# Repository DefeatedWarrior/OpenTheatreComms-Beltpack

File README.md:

# OpenTheatreComms beltpack

An open, DIY full-duplex wireless theatre intercom beltpack in the spirit of the Hollyland Solidcom M1 and Clear-Com FreeSpeak II.
It uses an ESP32-S3 with an LR2021 radio on 915–928 MHz (Australia), talks to PoE base stations over a 20 ms TDMA frame,
and is 3D printed and hand-assembled.

## What's here

| Path | Contents |
|---|---|
| `cad/final_bp.py` | CadQuery model of the whole beltpack: shells, TPU caps, dials, keys, both PCBs and every bought part as a datasheet envelope |
| `cad/geom.py` | Shared shape helpers (the curved pill plan, edge fillets, the flat-top frame) |
| `cad/clash.py` | Pairwise interference check across all 71 parts |
| `cad/export_boards.py` | KiCad hand-off: DXF outlines with true arcs, placement layers and dimensioned drawings |
| `cad/make_kicad.py`, `cad/make_enclosure_ref.py` | Build the KiCad projects (needs KiCad's `pcbnew` Python module) and the enclosure STEP |
| `cad/section.py`, `cad/size_table.py` | Section drawings and the placement CSV |
| `cad/out/beltpack_final.step` | Full assembly (STEP) |
| `cad/out/stl/` | Every printed part as STL |
| `cad/out/kicad/` | Board outlines (DXF), drawings, placement CSV |
| `kicad/` | Finished KiCad projects, each with a README and `fab/` outputs (Gerbers, drill, BOM, placement, schematic PDF, previews): beltpack main board, top board, pack lid and dock contact board, and the base station carrier |
| `pcb/` | The Python that generates each board: `design.py` (parts and nets), schematic, placement, routing, finishing and fab outputs |
| `order/` | The v1 order for 2 beltpacks + 1 base station: JLCPCB board settings and stencils, the LCSC cart (all parts hand-fitted), other suppliers, and the assembly guide (`ORDER_README.md`) |
| `renders/` | Render sheet and individual renders |
| `viewer/` | Interactive three.js viewer (open `viewer/index.html` from a local web server) |

The firmware and system architecture, the BOM and the open decisions live in the
[architecture doc](https://claude.ai/artifact/WxYNr5Pqa9sfHdBBrxbrdB). The [3D viewer](https://claude.ai/artifact/3vzgMREVLjprdXMhVy1U9x)
is the same page as `viewer/`.

## The pack

- **Size:** 105 × 77 × 30 mm shell (108 × 81 × 35 mm with the TPU caps, 39 mm deep with the belt plate). The back follows a 400 mm radius to sit on the hip.
- **Controls:** four talk keys and a 1.3 in OLED on the flat top, a detented dial at each round end, Back / Function / Menu in a recessed panel on the front.
- **Bottom:** XLR-4 male (D-type), power button, USB-C, 3.5 mm TRRS, flashlight.
- **Power:** a 104050 Li-ion pack (2500 mAh) forms the back of the case; the belt plate slides up its rails and locks it in. Three spring pins carry battery +, NTC and battery −; a JST XH 2-pin socket (J11) on the main board is a second battery input for a wired cell or bench supply.
- **Dock contacts:** four contact pads in the case bottom (VBUS, D+, D−, GND) on a small contact board lying in the case bottom under
  the battery pack, cabled flat to J12, a vertical socket at the main board's bottom edge. A dock charges the pack and talks USB to it (pairing, settings, firmware); a diode keeps the USB-C's 5 V off the pads.
- **Boards:** a curved top PCB (99.8 × 26.5 mm) under the keys carrying the OLED, six RGB lights on an LP5024 driver and both encoders, and a vertical main PCB (87.5 × 64.5 mm) carrying the MCU, radio, codec, power and connectors. A 10-way JST SH cable links them.
- **Radio:** an Elecrow LR2021 module on 915–928 MHz with switched antenna diversity: a PE4259-type switch (HX4259-63) picks between two flex antennas, one inside each round end, every frame.

## Rebuilding

Needs Python 3 with `cadquery`, `ezdxf`, `matplotlib` and `Pillow`.

```sh
cd cad
python3 final_bp.py       # model, STEP, GLB, STLs, parts_final.json (about a minute)
python3 clash.py          # interference check: expect "CLASHES: 0"
python3 export_boards.py  # DXFs and drawings into out/kicad
python3 section.py        # section drawings
python3 size_table.py     # placement.csv
python3 build_viewer.py   # viewer/index.html + viewer/beltpack.json
python3 make_enclosure_ref.py && python3 make_kicad.py   # KiCad projects in ../kicad (needs KiCad 7+)
```

## Base station

A 150 x 90 mm 2-layer carrier for a Waveshare ESP32-P4-NANO (Ethernet for AES67, optional PoE), with the same LR2021 radio and
two edge SMA antennas, a DC input (7-24 V buck), a 1.3 in OLED, four talk keys with RGB lights, eight beltpack lights and a menu dial.
It has no audio of its own: the operator's headset is a beltpack plugged into the base by USB-C. See `kicad/base_pcb/README.md`.

## Status

**Boards:** all five are laid out and pass KiCad DRC with 0 errors and 0 unconnected pads. The v1 order (`order/`) is ready, at about
A$410 for 2 beltpacks + 1 base station, with every part hand-fitted from solder-paste stencils.

**Case:** to be redone around the cheaper parts chosen for v1. The pack pads move to 4.0 mm from the main board's back face for the
Xinyangze spring pins; it needs room for the 7 mm JST XH socket on the main board's front and the Alps EC11 dials' shaft length, and a pocket in
the bottom for the dock contact board. The base station's dock side (spring pins, switched VBUS, USB host) is still to design.

**Reference model notes:**

The CAD model was the reference for the KiCad layout. A few part envelopes are typical sizes still to check against
the exact parts you buy: the encoder body height, the XLR D-flange and depth, USB4105, the PTS815 height variant, the side tact switch,
the JST SH bodies and where the OLED panel's active area sits on its glass. See `cad/out/kicad/README.md`.

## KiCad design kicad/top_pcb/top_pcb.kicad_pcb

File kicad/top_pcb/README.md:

# Top PCB build scripts

The top PCB (keys, six RGB lights, OLED connector, both dials, IO expander, LED driver, link to the main PCB) is generated
from one file, `design.py`, which holds every part, its nets, its schematic position and its board position.

```sh
python3 make_lib.py                                   # the OLED tail pads footprint and the LP5024 symbol
python3 make_sch.py                                   # out/top_pcb.kicad_sch (KiCad 7 format, real library symbols)
kicad-cli sch export netlist --format kicadsexpr -o out/top_pcb.net out/top_pcb.kicad_sch
python3 chknet.py out/top_pcb.net                     # every net must match design.py
python3 make_pcb.py                                   # place, pre-route the FPC fan-outs, GND fanouts, route with Freerouting 1.9 -> out/routed.kicad_pcb
                                                      # (make_pcb.py import: re-import the last routing session without rerouting)
python3 finish_pcb.py                                 # GND pours, stitching, repair, DRC -> ../kicad_proj/top_pcb/
python3 make_fab.py                                   # Gerbers, drill, placement, BOM, assembly PDFs -> ../kicad_proj/top_pcb/fab/
```

Needs KiCad 7+ (`pcbnew` Python module and `kicad-cli`), the KiCad symbol and footprint libraries, Java, `xvfb-run`,
Freerouting 1.9.0 (`FREEROUTING` in `make_pcb.py`), and Python `shapely` and `cairosvg`.

| File | Role |
|---|---|
| `design.py` | Parts, nets, schematic and board positions; `OLED_PIN1_AT_PLUS_X` flips the panel pin order |
| `make_lib.py` | Writes `lib/OpenTheatreComms.pretty` (the 30 solder pads, 0.7 mm, for the OLED panel's tail) and `lib/OpenTheatreComms.kicad_sym` (TI LP5024) |
| `symlib.py`, `sexp.py` | Read KiCad library symbols, read and write S-expressions |
| `make_sch.py`, `chknet.py` | Schematic writer and netlist check |
| `pcbgeom.py` | Board-frame transforms, copper model for via placement, per-net connectivity check |
| `make_pcb.py`, `finish_pcb.py` | Board build |
| `make_fab.py`, `render.py` | Fab outputs and PNG previews |
| `template/` | The starter board (outline, holes, guides, enclosure 3D reference) the build starts from |

Board frame: origin at the board centre, +X right, +Y toward the hip (back) edge, viewed from above (F = top).

## Lights

Six common-anode RGB LEDs (Lite-On LTST-C19HE1WT, 1.6 x 1.6 mm): D1-D4 above the four talk keys, D5 and D6 under the
left and right status light pipes. Each is driven by a TI LP5024 (U2, on the bottom side) on the board's I2C bus, so
every LED takes any colour and brightness from firmware:

| Light | LP5024 channel | Outputs (R, G, B) |
|---|---|---|
| D1, talk key 1 | LED0 | OUT0-OUT2 |
| D2, talk key 2 | LED1 | OUT3-OUT5 |
| D5, status left | LED2 | OUT6-OUT8 |
| D3, talk key 3 | LED3 | OUT9-OUT11 |
| D4, talk key 4 | LED4 | OUT12-OUT14 |
| D6, status right | LED5 | OUT15-OUT17 |

The order follows the board (each light's lines leave the driver on the side facing it); `LED_CH` in `design.py` holds it.

- **Current:** R1 = 15k sets 4.9 mA full scale per colour (105 x 0.7 V / R1); the 12-bit PWM dims from there. The low
  current leaves the green and blue chips (about 2.7 V at 5 mA) headroom on the 3.3 V anode supply.
- **I2C addresses on the beltpack bus:** LP5024 0x28 (ADDR1 = ADDR0 = GND). Its broadcast address is 0x3C, so the OLED
  is strapped to **0x3D** (D/C# high). The IO expander is 0x20.
- **EN** comes from the expander's P05: its internal pull-up holds the driver on from power-up; firmware can pulse it low
  to reset the driver. Expander P10-P17 are now free.

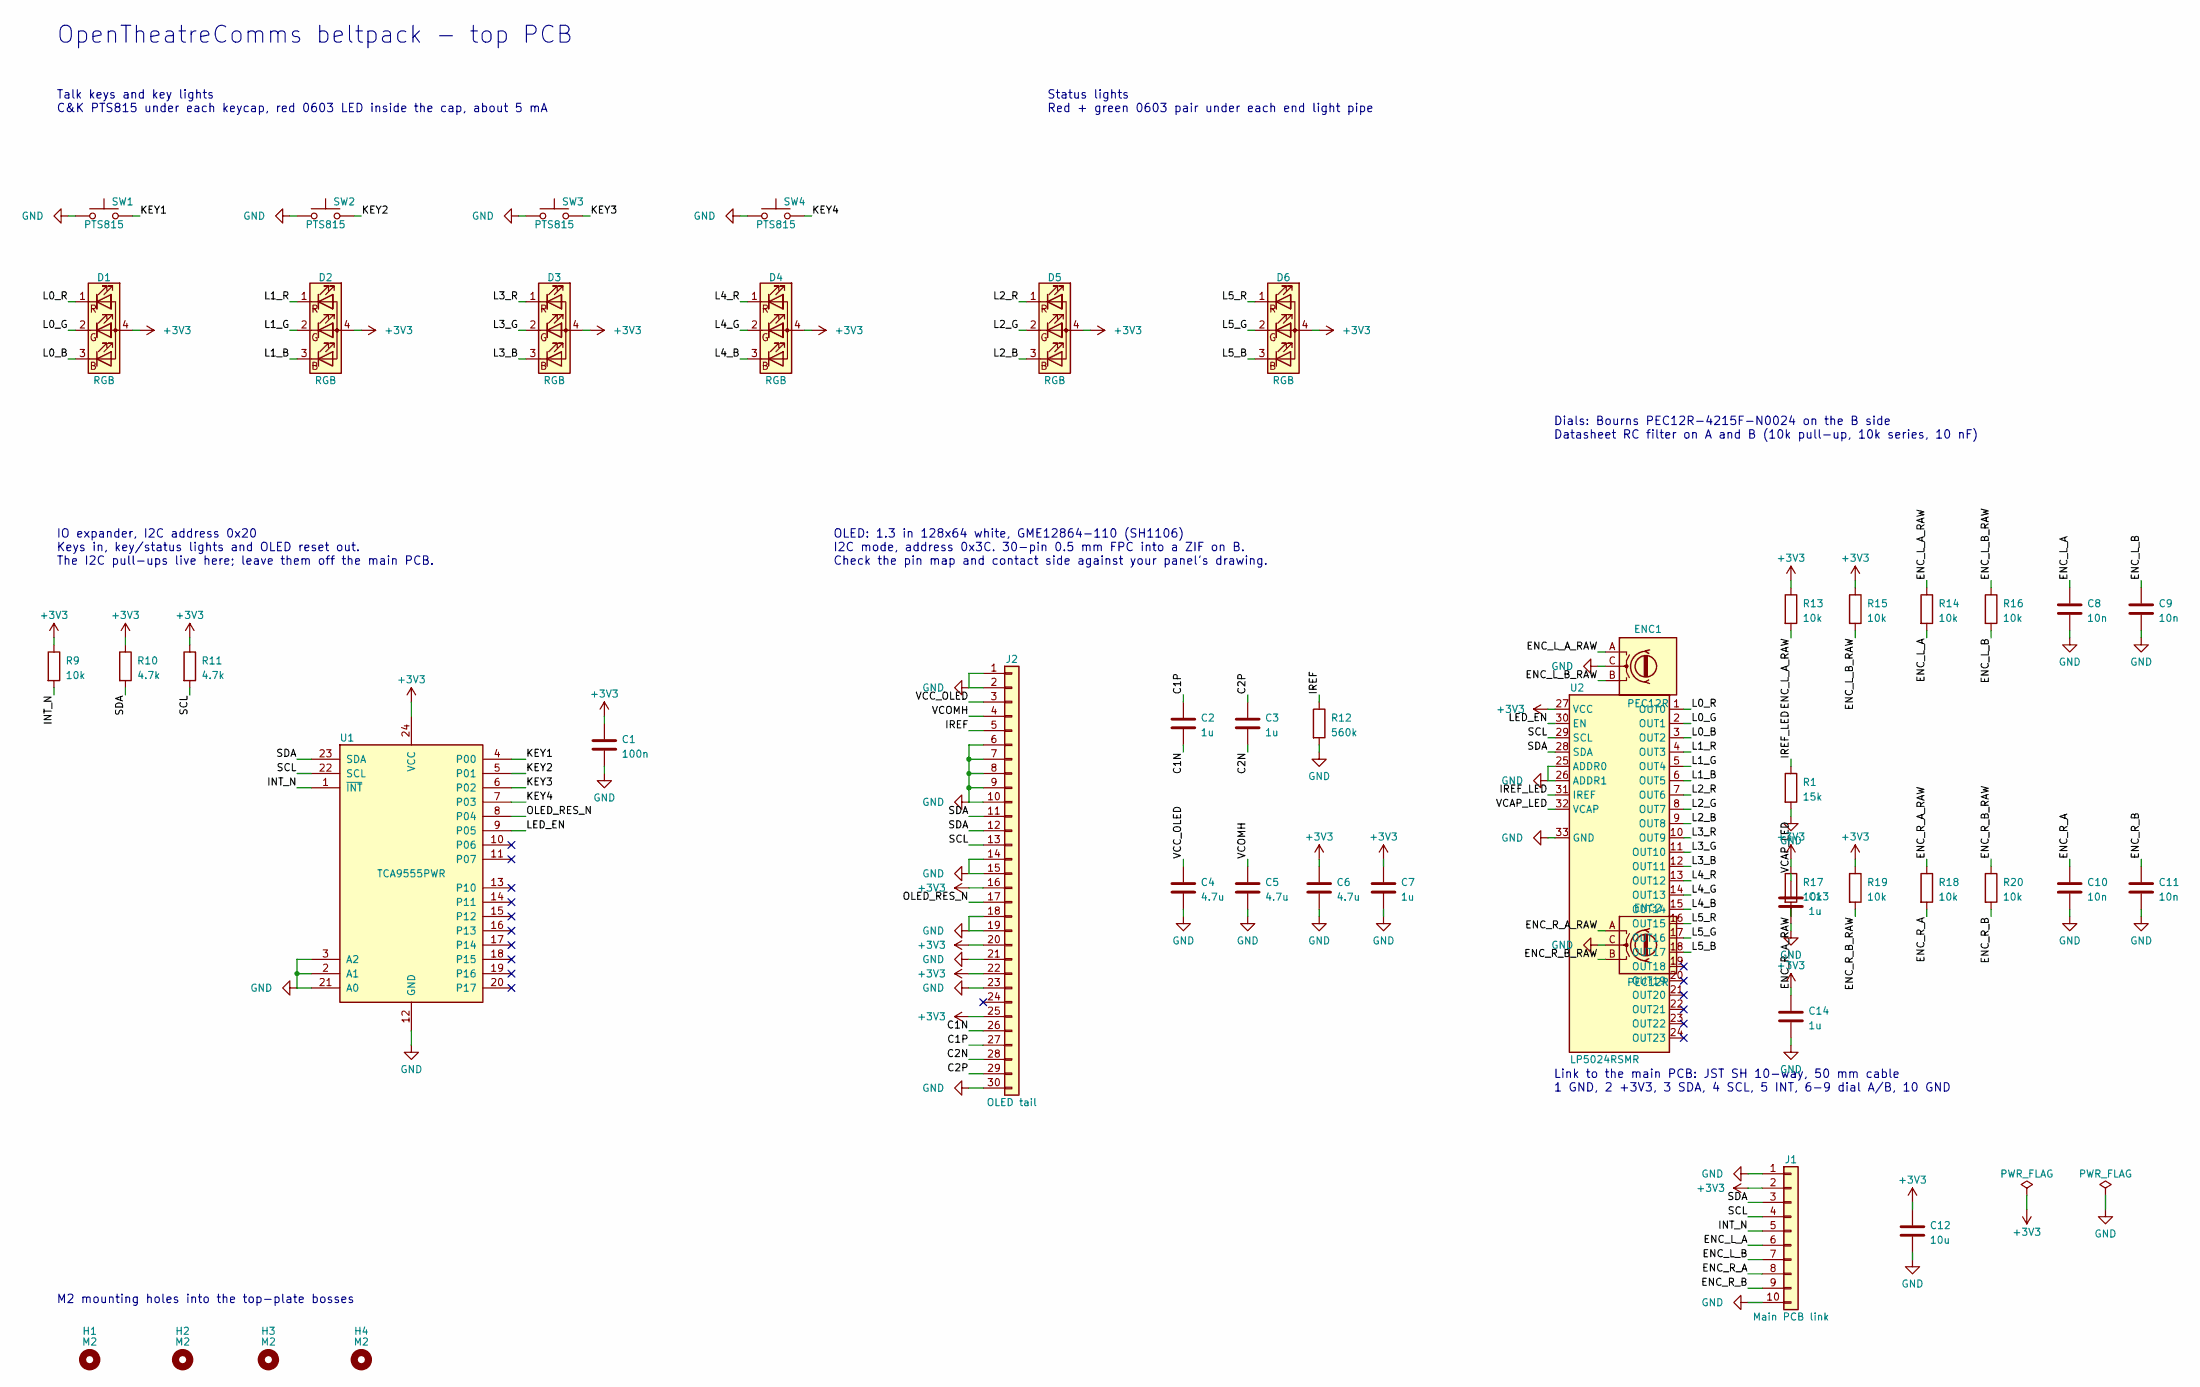
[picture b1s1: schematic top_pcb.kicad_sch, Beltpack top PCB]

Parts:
C1: 100n; C_0603_1608Metric_Pad1.08x0.95mm_HandSolder; MPN 0603 X7R 50 V
C2, C3, C13, C14: 1u; C_0603_1608Metric_Pad1.08x0.95mm_HandSolder; MPN 0603 X5R
C4, C5: 4.7u; C_0603_1608Metric_Pad1.08x0.95mm_HandSolder; MPN 0603 X5R 25 V
C6: 4.7u; C_0603_1608Metric_Pad1.08x0.95mm_HandSolder; MPN 0603 X5R 10 V
C7: 1u; C_0603_1608Metric_Pad1.08x0.95mm_HandSolder; MPN 0603 X5R 10 V
C8, C9, C10, C11: 10n; C_0603_1608Metric_Pad1.08x0.95mm_HandSolder; MPN 0603 X7R 50 V
C12: 10u; C_0603_1608Metric_Pad1.08x0.95mm_HandSolder; MPN 0603 X5R 10 V
D1, D2, D3, D4, D5, D6: RGB; LED_LiteOn_LTST-C19HE1WT; MPN Lite-On LTST-C19HE1WT
ENC1, ENC2: PEC12R; RotaryEncoder_Bourns_Vertical_PEC12R-3x17F-Nxxxx; MPN Alps EC11N1520402
H1, H2, H3, H4: M2; MountingHole_2.2mm_M2
J1: Main PCB link; JST_SH_BM10B-SRSS-TB_1x10-1MP_P1.00mm_Vertical; MPN JST BM10B-SRSS-TB
J2: OLED tail; OLED_Tail_30P_0.7mm_Solder; MPN OLED panel tail soldered to pads (no pa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
R1: 15k; R_0603_1608Metric_Pad0.98x0.95mm_HandSolder; MPN 0603 1%
R9, R13, R14, R15, R16, R17, R18, R19, R20: 10k; R_0603_1608Metric_Pad0.98x0.95mm_HandSolder; MPN 0603 1%
R10, R11: 4.7k; R_0603_1608Metric_Pad0.98x0.95mm_HandSolder; MPN 0603 1%
R12: 560k; R_0603_1608Metric_Pad0.98x0.95mm_HandSolder; MPN 0603 1%
SW1, SW2, SW3, SW4: PTS815; SW_SPST_PTS810; MPN C&K PTS815 SJM 250 SMTR LFS
U1: TCA9555PWR; TSSOP-24_4.4x7.8mm_P0.65mm; MPN TI TCA9555PWR
U2: LP5024RSMR; VQFN-32-1EP_4x4mm_P0.4mm_EP2.8x2.8mm; MPN TI LP5024RSMR

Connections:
+3V3: C1.1, C6.1, C7.1, C12.1, C14.1, D1.4 (A), D2.4 (A), D3.4 (A), D4.4 (A), D5.4 (A), D6.4 (A), J1.2, J2.16, J2.20, J2.22, J2.25, R9.1, R10.1, R11.1, R13.1, R15.1, R17.1, R19.1, U1.24 (VCC), U2.27 (VCC)
/C1N: C2.2, J2.26
/C1P: C2.1, J2.27
/C2N: C3.2, J2.28
/C2P: C3.1, J2.29
/ENC_L_A: C8.1, J1.6, R14.2
/ENC_L_A_RAW: ENC1.A, R13.2, R14.1
/ENC_L_B: C9.1, J1.7, R16.2
/ENC_L_B_RAW: ENC1.B, R15.2, R16.1
/ENC_R_A: C10.1, J1.8, R18.2
/ENC_R_A_RAW: ENC2.A, R17.2, R18.1
/ENC_R_B: C11.1, J1.9, R20.2
/ENC_R_B_RAW: ENC2.B, R19.2, R20.1
/INT_N: J1.5, R9.2, U1.1 (~INT)
/IREF: J2.5, R12.1
/IREF_LED: R1.1, U2.31 (IREF)
/KEY1: SW1.2, U1.4 (P00)
/KEY2: SW2.2, U1.5 (P01)
/KEY3: SW3.2, U1.6 (P02)
/KEY4: SW4.2, U1.7 (P03)
/L0_B: D1.3 (BK), U2.3 (OUT2)
/L0_G: D1.2 (GK), U2.2 (OUT1)
/L0_R: D1.1 (RK), U2.1 (OUT0)
/L1_B: D2.3 (BK), U2.6 (OUT5)
/L1_G: D2.2 (GK), U2.5 (OUT4)
/L1_R: D2.1 (RK), U2.4 (OUT3)
/L2_B: D5.3 (BK), U2.9 (OUT8)
/L2_G: D5.2 (GK), U2.8 (OUT7)
/L2_R: D5.1 (RK), U2.7 (OUT6)
/L3_B: D3.3 (BK), U2.12 (OUT11)
/L3_G: D3.2 (GK), U2.11 (OUT10)
/L3_R: D3.1 (RK), U2.10 (OUT9)
/L4_B: D4.3 (BK), U2.15 (OUT14)
/L4_G: D4.2 (GK), U2.14 (OUT13)
/L4_R: D4.1 (RK), U2.13 (OUT12)
/L5_B: D6.3 (BK), U2.18 (OUT17)
/L5_G: D6.2 (GK), U2.17 (OUT16)
/L5_R: D6.1 (RK), U2.16 (OUT15)
/LED_EN: U1.9 (P05), U2.30 (EN)
/OLED_RES_N: J2.17, U1.8 (P04)
/SCL: J1.4, J2.13, R11.2, U1.22 (SCL), U2.29 (SCL)
/SDA: J1.3, J2.11, J2.12, R10.2, U1.23 (SDA), U2.28 (SDA)
/VCAP_LED: C13.1, U2.32 (VCAP)
/VCC_OLED: C4.1, J2.3
/VCOMH: C5.1, J2.4
GND: C1.2, C4.2, C5.2, C6.2, C7.2, C8.2, C9.2, C10.2, C11.2, C12.2, C13.2, C14.2, ENC1.C, ENC2.C, J1.1, J1.10, J2.1, J2.2, J2.6, J2.7, J2.8, J2.9, J2.10, J2.14, J2.15, J2.18, J2.19, J2.21, J2.23, J2.30, R1.2, R12.2, SW1.1, SW2.1, SW3.1, SW4.1, U1.2 (A1), U1.3 (A2), U1.12 (GND), U1.21 (A0), U2.25 (ADDR0), U2.26 (ADDR1), U2.33 (GND)

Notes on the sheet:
Talk keys and key lights C&K PTS815 under each keycap, red 0603 LED inside the cap, about 5 mA
Status lights Red + green 0603 pair under each end light pipe
IO expander, I2C address 0x20 Keys in, key/status lights and OLED reset out. The I2C pull-ups live here; leave them off the main PCB.
OLED: 1.3 in 128x64 white, GME12864-110 (SH1106) I2C mode, address 0x3C. 30-pin 0.5 mm FPC into a ZIF on B. Check the pin map and contact side against your panel's drawing.
Dials: Bourns PEC12R-4215F-N0024 on the B side Datasheet RC filter on A and B (10k pull-up, 10k series, 10 nF)
Link to the main PCB: JST SH 10-way, 50 mm cable 1 GND, 2 +3V3, 3 SDA, 4 SCL, 5 INT, 6-9 dial A/B, 10 GND
M2 mounting holes into the top-plate bosses
OpenTheatreComms beltpack - top PCB

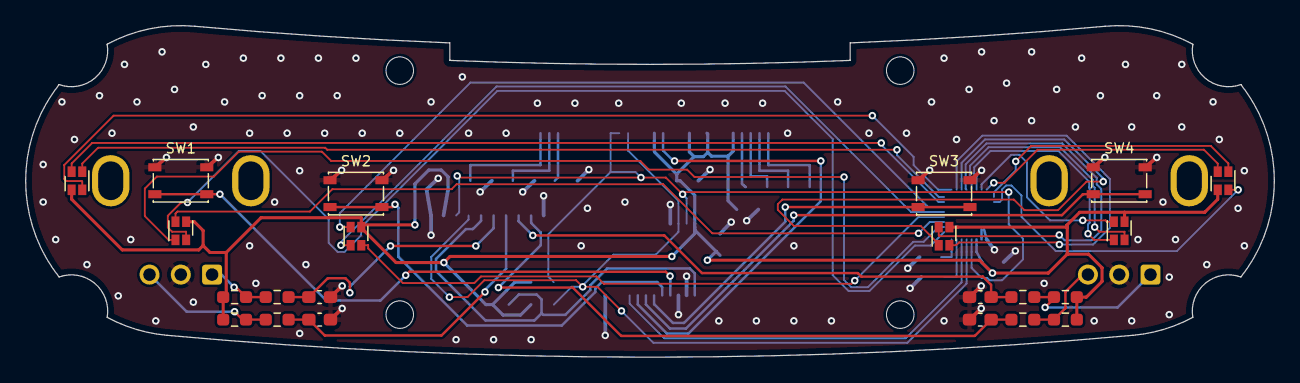
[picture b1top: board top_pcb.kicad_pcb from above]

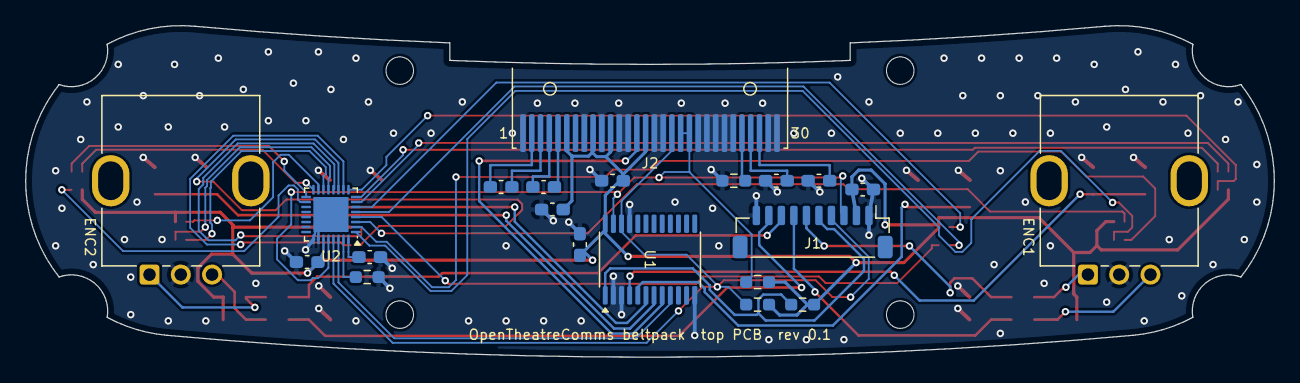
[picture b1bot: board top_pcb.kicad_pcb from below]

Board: 2 copper layers, 99.8 x 26.5 mm, 47 parts (21 on the bottom side), 46 nets.

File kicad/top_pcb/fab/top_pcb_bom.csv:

Qty,References,Value,Footprint,Part,Side,Notes
1,C1,100n,C_0603_1608Metric_Pad1.08x0.95mm_HandSolder,0603 X7R 50 V,bottom,U1 decoupling
4,C2 C3 C13 C14,1u,C_0603_1608Metric_Pad1.08x0.95mm_HandSolder,0603 X5R,bottom,
2,C4 C5,4.7u,C_0603_1608Metric_Pad1.08x0.95mm_HandSolder,0603 X5R 25 V,bottom,
1,C6,4.7u,C_0603_1608Metric_Pad1.08x0.95mm_HandSolder,0603 X5R 10 V,bottom,Charge-pump supply (VBAT pin)
1,C7,1u,C_0603_1608Metric_Pad1.08x0.95mm_HandSolder,0603 X5R 10 V,bottom,Logic supply (VDD pin)
4,C8 C9 C10 C11,10n,C_0603_1608Metric_Pad1.08x0.95mm_HandSolder,0603 X7R 50 V,top,
1,C12,10u,C_0603_1608Metric_Pad1.08x0.95mm_HandSolder,0603 X5R 10 V,bottom,"Bulk at the link connector, wired straight to its pins 1 and 2"
6,D1 D2 D3 D4 D5 D6,RGB,LED_LiteOn_LTST-C19HE1WT,Lite-On LTST-C19HE1WT,top,
2,ENC1 ENC2,PEC12R,RotaryEncoder_Bourns_Vertical_PEC12R-3x17F-Nxxxx,Alps EC11N1520402,bottom,
1,J1,Main PCB link,JST_SH_BM10B-SRSS-TB_1x10-1MP_P1.00mm_Vertical,JST BM10B-SRSS-TB,bottom,JST SH 10-way top entry; 50 mm cable to SM10B on the main PCB tab
1,J2,OLED tail,OLED_Tail_30P_0.7mm_Solder,OLED panel tail soldered to pads (no part),bottom,"Solder pads for the panel's 30-lead tail (0.7 mm pitch). Standard 1.3 in SH1106 30-pin pin map; I2C (BS2..0 = 010), address 0x3D (SA0 = D/C# high: 0x3C is the LP5024 broadcast)"
1,R1,15k,R_0603_1608Metric_Pad0.98x0.95mm_HandSolder,0603 1%,bottom,"LP5024 full-scale current, 4.9 mA"
9,R9 R13 R14 R15 R16 R17 R18 R19 R20,10k,R_0603_1608Metric_Pad0.98x0.95mm_HandSolder,0603 1%,bottom/top,
2,R10 R11,4.7k,R_0603_1608Metric_Pad0.98x0.95mm_HandSolder,0603 1%,bottom,
1,R12,560k,R_0603_1608Metric_Pad0.98x0.95mm_HandSolder,0603 1%,bottom,Segment current reference: 560k per the panel reference circuit (12.5 uA max)
4,SW1 SW2 SW3 SW4,PTS815,SW_SPST_PTS810,C&K PTS815 SJM 250 SMTR LFS,top,
1,U1,TCA9555PWR,TSSOP-24_4.4x7.8mm_P0.65mm,TI TCA9555PWR,bottom,"16-bit I2C IO expander, 0x20, internal 100k pull-ups"
1,U2,LP5024RSMR,VQFN-32-1EP_4x4mm_P0.4mm_EP2.8x2.8mm,TI LP5024RSMR,bottom,"24-channel I2C RGB LED driver, 0x28: six RGB LEDs; EN from the expander (P05, high by its pull-up at power-up)"

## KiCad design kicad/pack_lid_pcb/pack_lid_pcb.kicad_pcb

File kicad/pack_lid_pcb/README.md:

# Beltpack pack lid PCB, rev 0.1

The battery pack's contact board. It sits in the recess in the pack's front face, under the main PCB's three Mill-Max
spring pins, and carries the cell's three leads to them: BAT+, the pack NTC, and BAT-.

| Front (faces the main PCB) | Back (faces the cell) |
|---|---|
|  |  |

| | |
|---|---|
| Size | 24 x 8 mm, 0.8 mm FR4, 2 layers |
| Finish | HASL (with lead) as ordered; the three 3 mm contact pads are bare. ENIG is the upgrade if contact ever gets flaky |
| Parts | None. Three contact pads, three plated wire holes for 0.25 mm2 (24 AWG) wire, and short front-side tracks |
| DRC | 0 errors, 0 unconnected. 4 warnings, both expected: the contact and wire pads have their library silk and courtyards moved off (they are copper, not parts), and the enclosure reference footprint has no library |

## Files

| Path | Contents |
|---|---|
| `pack_lid_pcb.kicad_sch`, `pack_lid_pcb.kicad_pcb` | Schematic and board |
| `fab/pack_lid_pcb_gerbers.zip` | Gerbers + Excellon drill, ready to upload |
| `fab/pack_lid_pcb_schematic.pdf`, `fab/pack_lid_pcb_drc.rpt` | Schematic print and the DRC report |

Order as: 2 layers, 0.8 mm, HASL (with lead) or ENIG, any mask colour. There's nothing to assemble: solder the cell's leads into the holes.

## Pads and wiring

| Contact pad (front) | Spring pin on the main PCB | Wire hole | Wire |
|---|---|---|---|
| J1 at x 6 | J8, battery + | J4 at x 2.2 | Cell + (red), after the cell's protection board |
| J2 at x 12 | J9, pack NTC | J5 at x 9.0 | NTC lead (yellow or white): a 10k B 3435 thermistor taped to the cell, other end to cell - |
| J3 at x 18 | J10, battery - | J6 at x 21.8 | Cell - (black), after the protection board |

The charger on the main PCB (R4 = 6.2k into its TEMP pin) expects the 10k NTC between NTC and BAT-. With a 2-wire
cell and no NTC, fit R5 on the main PCB instead: it ties TEMP to ground and turns the temperature check off.

## Check before ordering

1. **How the wires reach the lid.** The lid sits right against the cell, so wires can't run behind it, and the pack
   tray in the case model holds the cell with only 0.2 mm to spare. The tray needs a wire channel from the cell's
   protection board to the lid, ending at the lid's edge so the leads come in from the front. The solder joints then
   sit on the front face, where the main PCB leaves 2.8 mm or more above them.
2. **Pad wear.** The spring pins compress 0.8 mm onto the pads every time the pack goes in. HASL is fine for a
   prototype (wipe the pads with IPA if contact gets flaky); ENIG lasts longer.

## Rebuilding

Generated from `pcb_lid/design.py`: `python3 make_sch.py`, then `kicad-cli sch export netlist` and `python3 chknet.py`,
then `python3 make_pcb.py` and `python3 make_fab.py`.

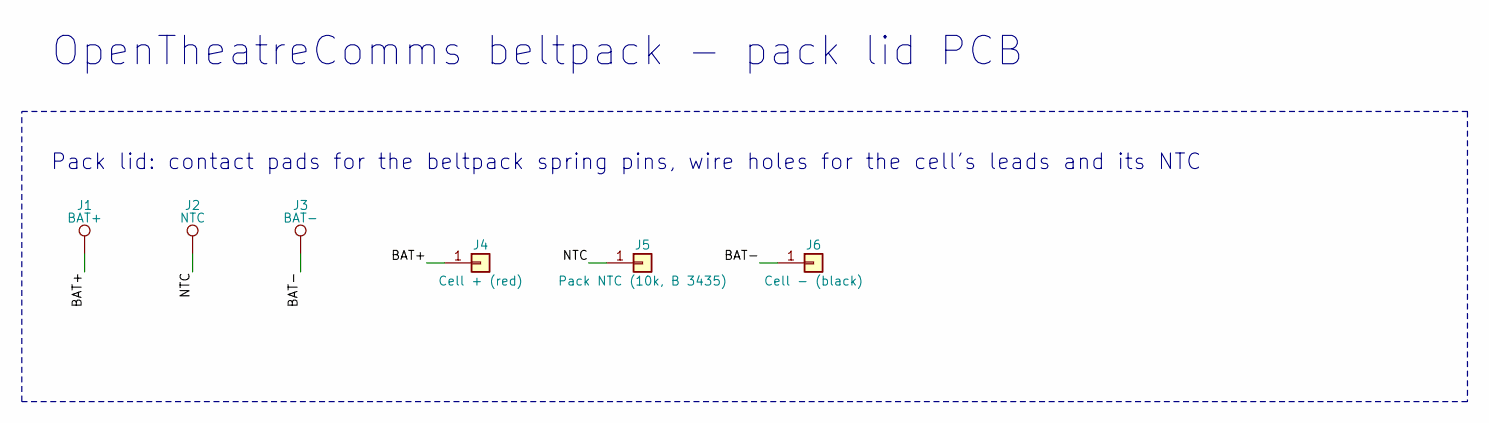
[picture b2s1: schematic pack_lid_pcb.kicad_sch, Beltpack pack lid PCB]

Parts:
J1: BAT+; TestPoint_Pad_D3.0mm; MPN PCB pad (ENIG)
J2: NTC; TestPoint_Pad_D3.0mm; MPN PCB pad (ENIG)
J3: BAT-; TestPoint_Pad_D3.0mm; MPN PCB pad (ENIG)
J4: Cell + (red); SolderWire-0.25sqmm_1x01_D0.65mm_OD1.7mm; MPN Wire, 0.25 mm2 (24 AWG)
J5: Pack NTC (10k, B 3435); SolderWire-0.25sqmm_1x01_D0.65mm_OD1.7mm; MPN Wire, 0.25 mm2 (24 AWG)
J6: Cell - (black); SolderWire-0.25sqmm_1x01_D0.65mm_OD1.7mm; MPN Wire, 0.25 mm2 (24 AWG)

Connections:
BAT+: J1.1, J4.1
BAT-: J3.1, J6.1
NTC: J2.1, J5.1

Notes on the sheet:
Pack lid: contact pads for the beltpack spring pins, wire holes for the cell's leads and its NTC
OpenTheatreComms beltpack - pack lid PCB

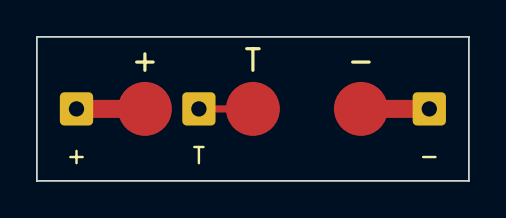
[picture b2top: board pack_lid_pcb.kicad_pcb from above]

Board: 2 copper layers, 24.0 x 8.0 mm, 6 parts (0 on the bottom side), 3 nets.

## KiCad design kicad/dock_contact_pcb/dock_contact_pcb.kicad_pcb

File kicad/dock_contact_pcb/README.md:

# Beltpack dock contact board, rev 0.1

The beltpack's dock contacts: four gold pads in the case bottom where the base station dock's spring pins land. They
carry USB, for charging and data (pairing, settings and firmware updates through the dock).

| | |
|---|---|
| Size | 22 x 11 mm, 0.8 mm FR4, 2 layers, HASL (with lead) as ordered, two M2 holes (2.2 mm) at x 1.8 and 20.2 |
| Outside face (F) | Four 2.5 mm bare pads at 4.0 mm pitch, 8.6 mm from the edge that faces the main board. Seen from outside, left to right: **GND, D+, D−, VBUS** |
| Inside face (B) | JST SH 4-pin side-entry socket (SM04B-SRSS-TB, 2.9 mm tall), mouth at the edge facing the main board: pin 1 VBUS, 2 D−, 3 D+, 4 GND |
| DRC | 0 errors, 0 unconnected. Four warnings: the test-point pads' library graphics were moved off the silkscreen |

## Wiring

The board lies flat in the case bottom, behind the main board and under the battery pack (x about 15–37, 14–25 mm back
from the front face), pads facing out through the bottom wall. Everything on its inside face is under 3.7 mm, inside the
5 mm strip below the pack. A flat 4-way JST SH cable (1.0 mm pitch, about 40–60 mm) runs straight forward from its socket
to the main board's **J12** (a vertical BM04B on the main board's back face, at the bottom edge, below the pack). Wire it
pin 1 to pin 1, and check with a meter before fitting: pre-made SH cables come both straight and reversed. On the main board:

- **VBUS** goes through **D12** (B5819W Schottky) into the pack's VBUS, so the dock charges the pack exactly like the
  USB-C does. The diode also keeps the USB-C's 5 V off these exposed pads when a cable is plugged in.
- **D+ / D−** join the ESP32-S3's USB lines, which the main board's USBLC6 (U1) already protects. Use the dock or the
  USB-C, not both at once.
- **GND** is the main board's ground.

## For the dock (base station side, to come)

- Spring pins at the same 4.0 mm pitch, landing on the pads' centres; 2.5 mm pads leave about ±0.8 mm of alignment
  tolerance for a 1 mm pin tip.
- Switch the dock's VBUS on only when a pack is sensed (or current-limit it), since the pins are exposed when empty.
- The dock is a USB host for D+/D− (the ESP32-P4 has USB host), or a USB hub to a PC for firmware updates.

## Case

The board sits in a pocket in the bottom wall with its pads flush with (or slightly proud of) the outside surface, held
by two M2 screws, its socket's mouth toward the main board. The pocket is behind the main board, so it stays clear of the
XLR, power button, USB-C, 3.5 mm and flashlight openings in front of it.

## Rebuilding

Generated from `pcb_dock/design.py`: `python3 make_sch.py`, `kicad-cli sch export netlist -o out/dock_contact_pcb.net
out/dock_contact_pcb.kicad_sch`, `python3 chknet.py out/dock_contact_pcb.net`, `python3 make_pcb.py`, `python3 make_fab.py`.

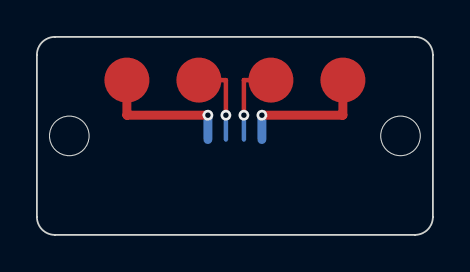
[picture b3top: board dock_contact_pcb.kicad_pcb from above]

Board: 2 copper layers, 22.0 x 11.0 mm, 7 parts (1 on the bottom side), 4 nets.

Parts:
H1, H2: M2; MountingHole_2.2mm_M2
J1: GND; TestPoint_Pad_D2.5mm
J2: D+; TestPoint_Pad_D2.5mm
J3: D-; TestPoint_Pad_D2.5mm
J4: VBUS; TestPoint_Pad_D2.5mm
J5: To main J12; JST_SH_SM04B-SRSS-TB_1x04-1MP_P1.00mm_Horizontal

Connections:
D+: J2.1, J5.3
D-: J3.1, J5.2
GND: J1.1, J5.4
VBUS: J4.1, J5.1
